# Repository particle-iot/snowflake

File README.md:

# Particle Snowflake

Welcome to the repository for the Particle Snowflake
, a limited edition [Particle P2](https://store.particle.io/products/p2-wi-fi-module-cut-tape-x10) powered PCBA in the form of a snowflake. The Snowflake provides a seasonal light show and plays a classic holiday tune.

This repository contains all of the firmware and hardware assets required to build the Particle Snowflake.

## Features

The Particle Snowflake has the following components to provide a complete experience straight out of the box:

- 36 individually addressable RGB LEDs to create various colors, patterns, and effects
- Onboard speaker to play festive tunes
- PDM microphone to enable additional features

## Repository Contents

This repository consists of a firmware folder, a hardware folder, and an assets folder.

### Firmware Folder

The firmware folder contains the source code and MP3 asset files that drive the operation of the Particle Snowflake. These include:

- Source code for the application firmware
- Various libraries to support the LEDs, audio and MP3 playback, capacitive touch button drivers, etc.
- MP3 asset files with preloaded message and holiday song

### Hardware Folder

The hardware folder contains detailed design files that can be used for manufacturing the Particle Snowflake. These include:

- Schematic files for the PCBA
- BRD files for the PCBA
- [A comprehensive Bill of Materials (BOM)](./hardware/schematic-pcb/snowflake-hw-v1.0.1/snowflake v1.01 Bom .xlsx)
- Illustrator files for the silkscreen artwork

### Asset Folder

The asset folder contains images and a video illustrating various aspects of the Particle Snowflake. These include:

- [Front of PCBA](./media/Snowflake_Front_Midnight.png)
- [Back of PCBA](./media/Snowflake_Back_Midnight.png)
- [Video of the various light patterns](./media/Snowflake_Action.mp4)

## Usage

Feel free to use these designs as a reference for creating your own Particle Snowflake or use them directly in your designs. 

## Contributing

As an open-source project, we encourage contributions and suggestions. If you have an idea for an improvement or notice a bug, please open an issue or submit a pull request.

## License

This project is open source and available under the [Apache License 2.0](LICENSE).

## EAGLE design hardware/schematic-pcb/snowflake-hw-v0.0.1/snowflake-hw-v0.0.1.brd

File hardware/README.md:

# snowflake-hw
Hardware design repository for Particle Snowflake

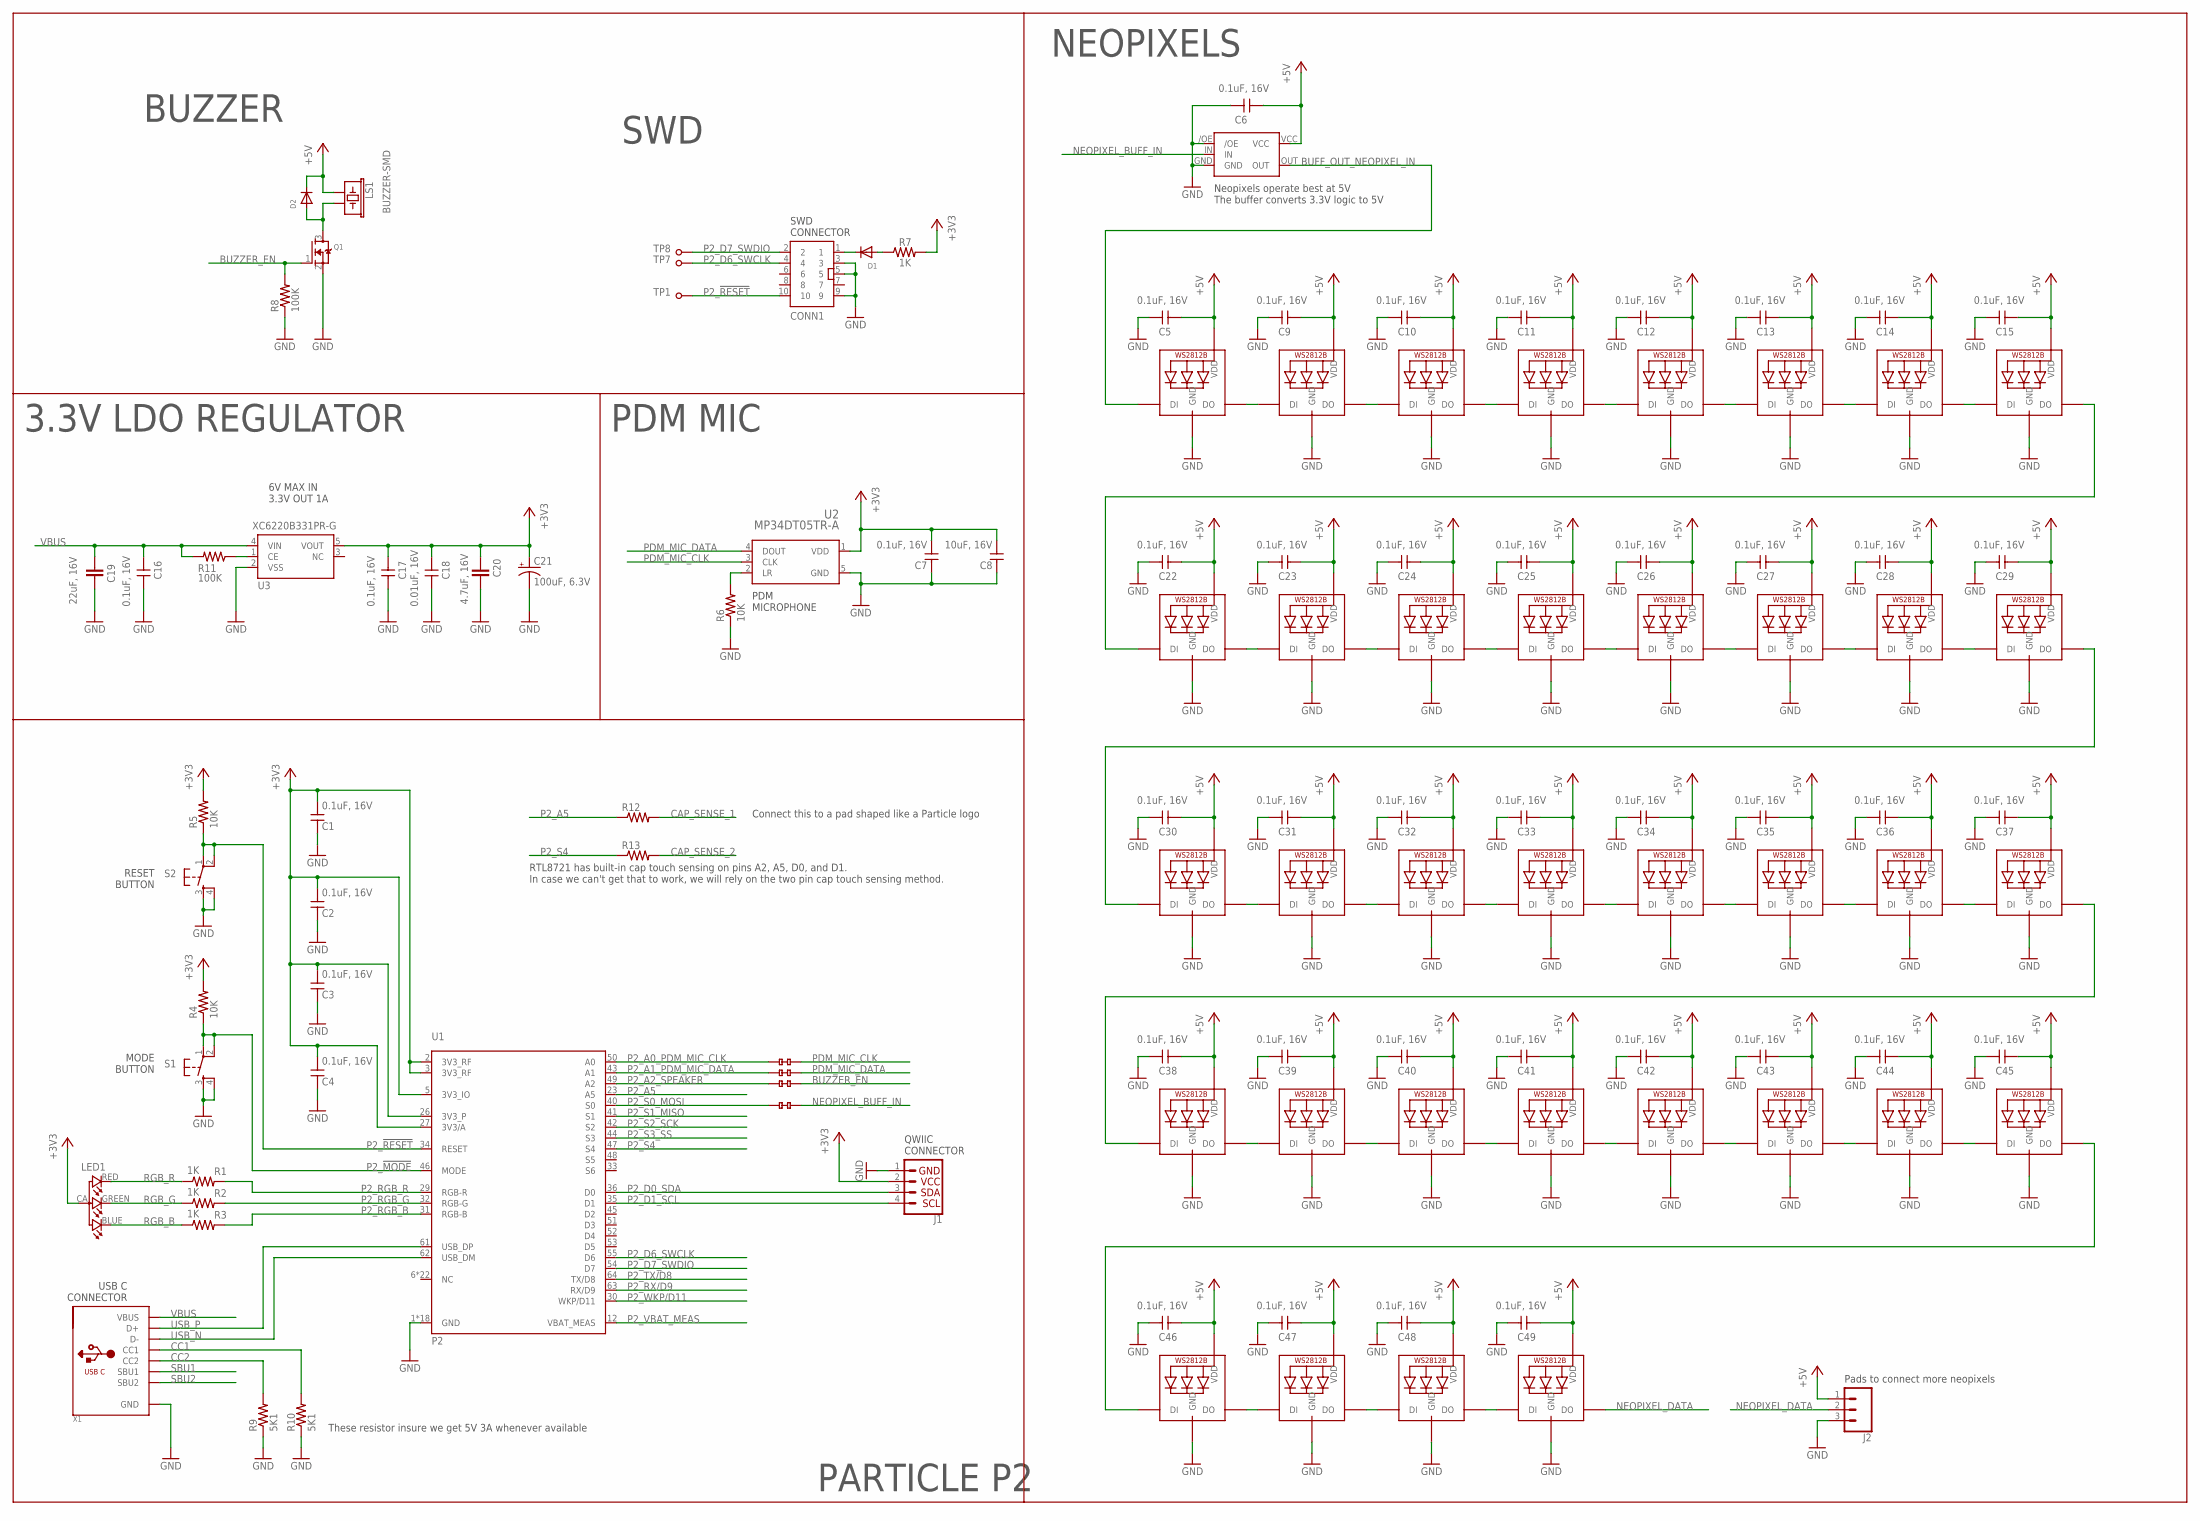
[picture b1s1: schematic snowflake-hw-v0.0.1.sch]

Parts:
C1, C2, C3, C4, C5, C6, C7, C9, C10, C11, C12, C13, C14, C15, C16, C17, C22, C23, C24, C25, C26, C27, C28, C29, C30, C31, C32, C33, C34, C35, C36, C37, C38, C39, C40, C41, C42, C43, C44, C45, C46, C47, C48, C49: 0.1uF, 16V; C0603_P
C8: 10uF, 16V; C0603_P
C18: 0.01uF, 16V; C0603_P
C19: 22uF, 16V; C0805
C20: 4.7uF, 16V; C0805
C21: 100uF, 6.3V; PANASONIC_C
CONN1: CONN5X2; CONN5X2_1.27
D1, D2: DIODESOD-123; SOD-123
J1: QWIIC_CONNECTORJS-1MM; 1X04_1MM_RA
J2: CONN_031X03_NO_SILK; 1X03_NO_SILK
LED1: RGB-LED-CLMVB-FKARGB; PLCC4-2MM-RGB
LED2, LED3, LED4, LED5, LED6, LED7, LED8, LED9, LED10, LED11, LED12, LED13, LED14, LED15, LED16, LED17, LED18, LED19, LED20, LED21, LED22, LED23, LED24, LED25, LED26, LED27, LED28, LED29, LED30, LED31, LED32, LED33, LED34, LED35, LED36, LED37: WS2812B_SK6812E; NEO3535_REVERSE
LS1: BUZZER-SMD; BUZZER-CCV
Q1: MOSFET-NREFLOW; SOT23
R1, R2, R3, R7: 1K; R0603_P
R4, R5, R6: 10K; R0603_P
R8, R11: 100K; R0603_P
R9, R10: 5K1; R0603_P
R12, R13: RES_0603; R0603_P
S1, S2: TAC_SWITCHSMD; TACTILE_SWITCH_SMD
TP1, TP7, TP8: TP-1.5MM; TP
U1: P2
U2: MP34DT05TR-A; MP34DT05TR-A_STM
U3: XC6220B331PR-G; SOT-89-5_TOR-M
U$1: NL17SZ125SOT553; SOT-553
U$2, U$3, U$4, U$15: JMP_0603_NC
X1: USB_C; USB_C_CUSB31-CFM2AX-01-X

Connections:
+3V3: C1.1, C2.1, C3.1, C4.1, C7.1, C8.1, C17.2, C18.1, C20.1, C21.+, J1.2 (VCC), LED1.CA (1), R4.2, R5.2, R7.2, U1.2 (3V3_RF), U1.3 (3V3_RF), U1.5 (3V3_IO), U1.26 (3V3_P), U1.27 (3V3/A), U2.1 (VDD), U3.5 (VOUT)
+5V: C5.2, C6.2, C9.2, C10.2, C11.2, C12.2, C13.2, C14.2, C15.2, C22.2, C23.2, C24.2, C25.2, C26.2, C27.2, C28.2, C29.2, C30.2, C31.2, C32.2, C33.2, C34.2, C35.2, C36.2, C37.2, C38.2, C39.2, C40.2, C41.2, C42.2, C43.2, C44.2, C45.2, C46.2, C47.2, C48.2, C49.2, D2.C, J2.1, LED2.1-VDD (VDD), LED3.1-VDD (VDD), LED4.1-VDD (VDD), LED5.1-VDD (VDD), LED6.1-VDD (VDD), LED7.1-VDD (VDD), LED8.1-VDD (VDD), LED9.1-VDD (VDD), LED10.1-VDD (VDD), LED11.1-VDD (VDD), LED12.1-VDD (VDD), LED13.1-VDD (VDD), LED14.1-VDD (VDD), LED15.1-VDD (VDD), LED16.1-VDD (VDD), LED17.1-VDD (VDD), LED18.1-VDD (VDD), LED19.1-VDD (VDD), LED20.1-VDD (VDD), LED21.1-VDD (VDD), LED22.1-VDD (VDD), LED23.1-VDD (VDD), LED24.1-VDD (VDD), LED25.1-VDD (VDD), LED26.1-VDD (VDD), LED27.1-VDD (VDD), LED28.1-VDD (VDD), LED29.1-VDD (VDD), LED30.1-VDD (VDD), LED31.1-VDD (VDD), LED32.1-VDD (VDD), LED33.1-VDD (VDD), LED34.1-VDD (VDD), LED35.1-VDD (VDD), LED36.1-VDD (VDD), LED37.1-VDD (VDD), LS1.+ (1), U$1.VCC
BUFF_OUT_NEOPIXEL_IN: LED2.4-DIN (DI), U$1.OUT
BUZZER_EN: Q1.1 (G), R8.2, U$2.2
CAP_SENSE_1: R12.2
CAP_SENSE_2: R13.2
CC1: R10.2, X1.A5 (CC1)
CC2: R9.2, X1.B5 (CC2)
GND: C1.2, C2.2, C3.2, C4.2, C5.1, C6.1, C7.2, C8.2, C9.1, C10.1, C11.1, C12.1, C13.1, C14.1, C15.1, C16.1, C17.1, C18.2, C19.2, C20.2, C21.-, C22.1, C23.1, C24.1, C25.1, C26.1, C27.1, C28.1, C29.1, C30.1, C31.1, C32.1, C33.1, C34.1, C35.1, C36.1, C37.1, C38.1, C39.1, C40.1, C41.1, C42.1, C43.1, C44.1, C45.1, C46.1, C47.1, C48.1, C49.1, CONN1.3, CONN1.5, CONN1.9, J1.1 (GND), J2.3, LED2.3-GND (GND), LED3.3-GND (GND), LED4.3-GND (GND), LED5.3-GND (GND), LED6.3-GND (GND), LED7.3-GND (GND), LED8.3-GND (GND), LED9.3-GND (GND), LED10.3-GND (GND), LED11.3-GND (GND), LED12.3-GND (GND), LED13.3-GND (GND), LED14.3-GND (GND), LED15.3-GND (GND), LED16.3-GND (GND), LED17.3-GND (GND), LED18.3-GND (GND), LED19.3-GND (GND), LED20.3-GND (GND), LED21.3-GND (GND), LED22.3-GND (GND), LED23.3-GND (GND), LED24.3-GND (GND), LED25.3-GND (GND), LED26.3-GND (GND), LED27.3-GND (GND), LED28.3-GND (GND), LED29.3-GND (GND), LED30.3-GND (GND), LED31.3-GND (GND), LED32.3-GND (GND), LED33.3-GND (GND), LED34.3-GND (GND), LED35.3-GND (GND), LED36.3-GND (GND), LED37.3-GND (GND), Q1.2 (S), R6.1, R8.1, R9.1, R10.1, S1.3, S1.4, S2.3, S2.4, U1.1 (GND), U1.4 (GND), U1.13 (GND), U1.15 (GND), U1.25 (GND), U1.28 (GND), U1.37 (GND), U1.39 (GND), U1.59 (GND), U1.65 (GND), U1.66 (GND), U1.67 (GND), U1.68 (GND), U1.69 (GND), U1.70 (GND), U1.71 (GND), U1.72 (GND), U1.73 (GND), U2.5 (GND), U3.2 (VSS), U$1./OE, U$1.GND, X1.A1B12 (GND), X1.B1A12 (GND)
unnamed: R6.2, U2.2 (LR)
unnamed: LED2.2-DOUT (DO), LED3.4-DIN (DI)
unnamed: LED3.2-DOUT (DO), LED4.4-DIN (DI)
unnamed: LED4.2-DOUT (DO), LED5.4-DIN (DI)
unnamed: LED5.2-DOUT (DO), LED6.4-DIN (DI)
unnamed: LED6.2-DOUT (DO), LED7.4-DIN (DI)
unnamed: LED7.2-DOUT (DO), LED8.4-DIN (DI)
unnamed: LED8.2-DOUT (DO), LED9.4-DIN (DI)
unnamed: D2.A, LS1.- (2), Q1.3 (D)
unnamed: R11.1, U3.1 (CE)
unnamed: LED10.2-DOUT (DO), LED11.4-DIN (DI)
unnamed: LED11.2-DOUT (DO), LED12.4-DIN (DI)
unnamed: LED12.2-DOUT (DO), LED13.4-DIN (DI)
unnamed: LED13.2-DOUT (DO), LED14.4-DIN (DI)
unnamed: LED14.2-DOUT (DO), LED15.4-DIN (DI)
unnamed: LED15.2-DOUT (DO), LED16.4-DIN (DI)
unnamed: CONN1.1, D1.C
unnamed: D1.A, R7.1
unnamed: LED16.2-DOUT (DO), LED17.4-DIN (DI)
unnamed: LED9.2-DOUT (DO), LED10.4-DIN (DI)
unnamed: LED24.2-DOUT (DO), LED25.4-DIN (DI)
unnamed: LED23.2-DOUT (DO), LED24.4-DIN (DI)
unnamed: LED22.2-DOUT (DO), LED23.4-DIN (DI)
unnamed: LED21.2-DOUT (DO), LED22.4-DIN (DI)
unnamed: LED20.2-DOUT (DO), LED21.4-DIN (DI)
unnamed: LED19.2-DOUT (DO), LED20.4-DIN (DI)
unnamed: LED18.2-DOUT (DO), LED19.4-DIN (DI)
unnamed: LED25.2-DOUT (DO), LED26.4-DIN (DI)
unnamed: LED26.2-DOUT (DO), LED27.4-DIN (DI)
unnamed: LED27.2-DOUT (DO), LED28.4-DIN (DI)
unnamed: LED28.2-DOUT (DO), LED29.4-DIN (DI)
unnamed: LED29.2-DOUT (DO), LED30.4-DIN (DI)
unnamed: LED30.2-DOUT (DO), LED31.4-DIN (DI)
unnamed: LED31.2-DOUT (DO), LED32.4-DIN (DI)
unnamed: LED32.2-DOUT (DO), LED33.4-DIN (DI)
unnamed: LED17.2-DOUT (DO), LED18.4-DIN (DI)
unnamed: LED34.2-DOUT (DO), LED35.4-DIN (DI)
unnamed: LED35.2-DOUT (DO), LED36.4-DIN (DI)
unnamed: LED36.2-DOUT (DO), LED37.4-DIN (DI)
unnamed: LED33.2-DOUT (DO), LED34.4-DIN (DI)
NEOPIXEL_BUFF_IN: U$1.IN, U$15.2
NEOPIXEL_DATA: J2.2, LED37.2-DOUT (DO)
P2_!MODE: R4.1, S1.1, S1.2, U1.46 (MODE)
P2_!RESET: CONN1.10, R5.1, S2.1, S2.2, TP1.TP, U1.34 (RESET)
P2_A0_PDM_MIC_CLK: U1.50 (A0), U$4.1
P2_A1_PDM_MIC_DATA: U1.43 (A1), U$3.1
P2_A2_SPEAKER: U1.49 (A2), U$2.1
P2_A5: R12.1, U1.23 (A5)
P2_D0_SDA: J1.3 (SDA), U1.36 (D0)
P2_D1_SCL: J1.4 (SCL), U1.35 (D1)
P2_D6_SWCLK: CONN1.4, TP7.TP, U1.55 (D6)
P2_D7_SWDIO: CONN1.2, TP8.TP, U1.54 (D7)
P2_RGB_B: R3.2, U1.31 (RGB-B)
P2_RGB_G: R2.2, U1.32 (RGB-G)
P2_RGB_R: R1.2, U1.29 (RGB-R)
P2_RX/D9: U1.63 (RX/D9)
P2_S0_MOSI: U1.40 (S0), U$15.1
P2_S1_MISO: U1.41 (S1)
P2_S2_SCK: U1.42 (S2)
P2_S3_SS: U1.44 (S3)
P2_S4: R13.1, U1.47 (S4)
P2_TX/D8: U1.64 (TX/D8)
P2_VBAT_MEAS: U1.12 (VBAT_MEAS)
P2_WKP/D11: U1.30 (WKP/D11)
PDM_MIC_CLK: U2.3 (CLK), U$4.2
PDM_MIC_DATA: U2.4 (DOUT), U$3.2
RGB_B: LED1.BLUE (2), R3.1
RGB_G: LED1.GREEN (3), R2.1
RGB_R: LED1.RED (4), R1.1
SBU1: X1.A8 (SBU1)
SBU2: X1.B8 (SBU2)
USB_N: U1.62 (USB_DM), X1.A7 (D-), X1.B7 (D-)
USB_P: U1.61 (USB_DP), X1.A6 (D+), X1.B6 (D+)
VBUS: C16.2, C19.1, R11.2, U3.4 (VIN), X1.A4B9 (VBUS), X1.B4A9 (VBUS)

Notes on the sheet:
6V MAX IN 3.3V OUT 1A
RESET BUTTON
MODE BUTTON
QWIIC CONNECTOR
SWD CONNECTOR
PDM MICROPHONE
RTL8721 has built-in cap touch sensing on pins A2, A5, D0, and D1. In case we can't get that to work, we will rely on the two pin cap touch sensing method.
Pads to connect more neopixels
3.3V LDO REGULATOR
PDM MIC
BUZZER
SWD
NEOPIXELS
PARTICLE P2
USB C CONNECTOR
Neopixels operate best at 5V The buffer converts 3.3V logic to 5V
Connect this to a pad shaped like a Particle logo
These resistor insure we get 5V 3A whenever available

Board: 2 copper layers, 120 parts (84 on the bottom side), 72 nets, no tracks yet.

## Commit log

2023-11-01 add README.md
2023-11-01 minor update for the music file receiver demo
2023-11-02 add RGB to indicate the progress of the file transfer
2023-11-02 get temperature from the NTC Thermistor
2023-11-13 Update the snowflake code
2023-11-13 Add new effect
2023-11-13 Add in settings to remember the led mode
2023-11-14 Add in:
    - mp3 player
    - tone player
    - updated audio file
    - hardware watchdog
2023-11-14 Move assets
2023-11-14 Update to work MP3 and tone
2023-11-15 Update stability
2023-11-15 Add new LED mode
2023-11-15 Add Blur
2023-11-15 Update blur settings
2023-11-15 Add in final effects
2023-11-15 Fixes MP3 player
2023-11-15 Fixed the crash
    Added in welcome message
2023-11-16 Fix tone player quality
    1.0.3
2023-11-16 Add welcome message
2023-11-16 Update version
2023-12-03 Add final HW files to repo
    Copied files from snowflake-hw repo.
2023-12-08 Don't flush the historic audio data in read API.
2023-12-12 Add Edge Impulse SDK and add build.mk for Particle project
2023-12-12 Enlarge the audio buffer for continuous audio demo
2023-12-12 add audio flush API
2023-12-12 new feature: add Egde Impulse demo
2023-12-13 fix cloud compile with filename case correction
2023-12-14 Add in app logic
2023-12-14 Push missing star mp3
2023-12-14 Update with working!
2023-12-14 Initial snowflake release
    Firmware: 1.0.5
    Hardware: 1.0.1
2023-12-14 Update sparkle keywork detection threshold
2023-12-14 Make a simple Readme until we update it later!
2023-12-14 Added readme and relevant assets
    Added readme along with the LICENSE file and various photos and a video.
2023-12-14 Update README.md
    Minor edit - removed old artifact from README.md template.
2023-12-14 Update assets folder name
    Updated assets folder name to media to distinguish it from OTA assets.
2023-12-14 Removed .DS_Store
2023-12-15 Update to model 15 with cleaned up training data
2023-12-16 Adjust model sensativies for detecting "sparkle" and also suppression window time.
2023-12-23 Added Particle.function cloudMode
    Cloud functions are fairly core to the Particle system so I added a Particle Console function to change modes. I haven't tested this code and I'm sure it could be cleaned up quite a bit since it dupl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
2023-12-23 +Particle Cloud mode function
    Cloud functions are pretty core to the Particle platform so I added a mode function so that the snowflake can change modes and sparkle via cloud.
    Also useful to show off sparkle via the Particle App/Web Console in loud rooms where the voice model currently fails.
    I haven't tested this code yet but except for mode=previous it pretty much copies button presses. Ultimately much of this code should be rolled into RgbStrip but I just wanted to get this in before C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
2023-12-23 Fixed hanging || in application.cpp
    Just removed a hanging || "or"
2023-12-23 fixed mode type in cloudMode case previous
    Added RgbStrip::MODES_T type
2023-12-31 Fix the settings so it can actually store more than 1 item.
    Add the ability to disable the sparkle via the particle console
    - send the content "sparkleEnable:0" to disable the sparkle voice recognition
    Release 1.2.00
2024-01-06 Disable sparkle by default
2024-01-07 Fix compile issue
2024-01-08 Fix Hanukkah mode Particle function
    Sending hanukkah through the particle cloud function wasn't work, the mode was missing.
2024-11-04 Update with blueprint
2024-11-04 Add in hardware tags
2024-12-16 update blueprint with more data and icons
2024-12-16 fix introduction indent
2024-12-17 add expertise level
2024-12-19 add external links
2024-12-20 Fix description
2026-02-20 fix asset image

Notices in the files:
parts and their libraries:
SparkFun-Connectors: Licensing: Creative Commons ShareAlike 4.0 International - https://creativecommons.org/licenses/by-sa/4.0
microbuilder: This work is placed in the public domain, and may be freely used for commercial and non-commercial work with the following conditions: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
